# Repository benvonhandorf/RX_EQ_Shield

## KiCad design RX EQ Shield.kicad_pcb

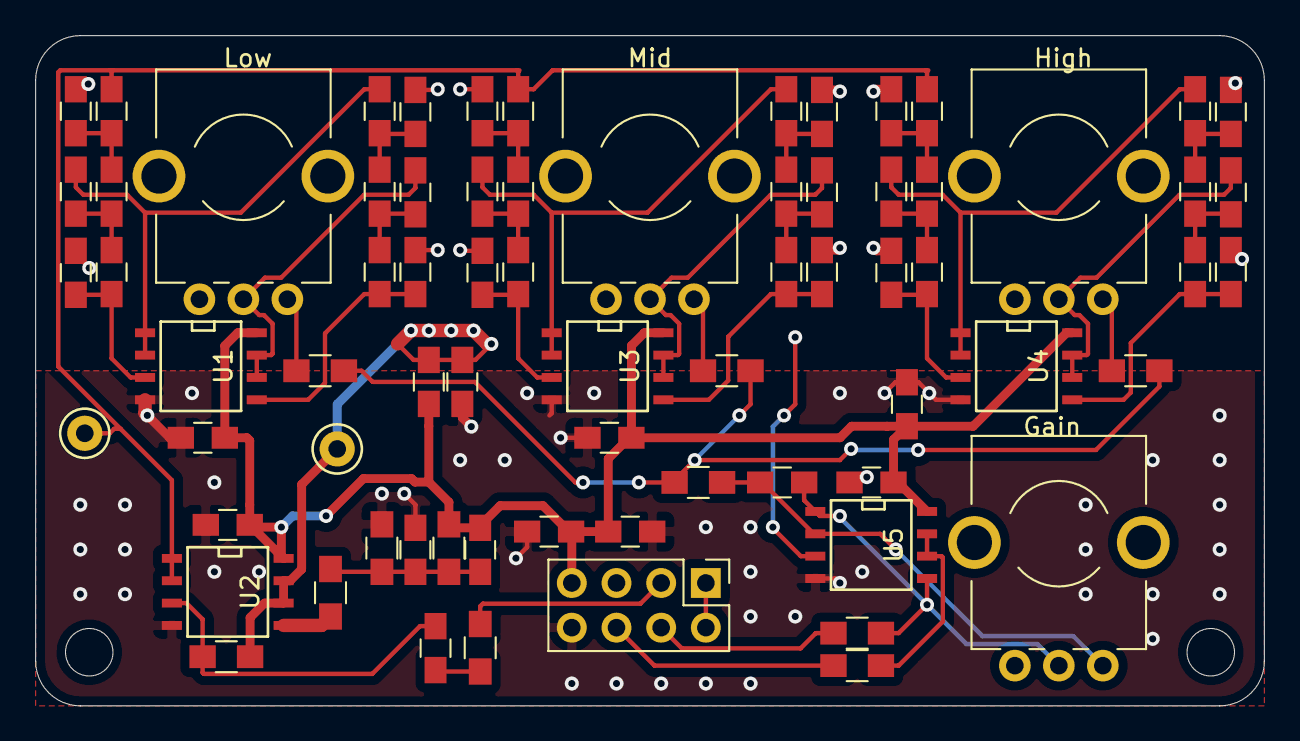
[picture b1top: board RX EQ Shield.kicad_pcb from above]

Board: 2 copper layers, 69.8 x 38.1 mm, 72 parts (0 on the bottom side), 43 nets.

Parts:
A1, A2, A3, A4, A5, A6, A7, A8, A9, A10, A11, A12, A13, A14, A15, A16, A17, A18: C; C_0805_HandSoldering
C1, C6, C8: 10uF; C_0805_HandSoldering
C2, C5, C7: 1uF; C_0805_HandSoldering
C3, C4, C9, C10, C11, C12: 0.1uF; C_0805_HandSoldering
C13: 1nF; C_0805_HandSoldering
FB1, FB2: Ferrite_Bead; L_0805_HandSoldering
J1: Conn_02x04_Odd_Even; Pin_Header_Straight_2x04_Pitch2.54mm
P1, P2, P3, P4, P5, P6, P7, P8, P9, P10, P11, P12, P13, P14, P15, P16, P17, P18: R; C_0805_HandSoldering
R1, R2: 1; R_0805_HandSoldering
R3, R4, R5, R6, R7, R8: 10k; R_0805_HandSoldering
R9: 4.7k; R_0805_HandSoldering
RV1, RV2, RV3, RV4: 10k; Potentiometer_TT_P090S-Top-Adjust
TP4, TP5: TestPoint; Test_Point_Keystone_5000-5004_Miniature
U1, U2, U3, U4, U5: OPA1678; SOIC-8-N

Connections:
+5V: C1.1, C2.1, C3.1, C5.1, C6.1, C9.1, C10.1, C11.1, C12.1, J1.7, R5.1, U1.8, U2.8, U3.8, U4.8, U5.8
/High EQ/AudioFilter/Audio_Out: A16.1, RV3.2, U4.6, U4.7
/High EQ/Audio_In: P1.2, P7.2, P13.2, TP4.1, U2.1, U2.2
/Low EQ/AudioFilter/Audio_Out: A4.1, RV1.2, U1.6, U1.7
/Mid EQ/AudioFilter/Audio_Out: A10.1, RV2.2, U3.6, U3.7
/Mixer/Audio_In: R3.1, R7.1, R8.1, R9.2
/Mixer/Audio_Out_L: C13.1, R1.2, RV4.2, U5.1, U5.5
/Mixer/Audio_Out_R: R2.2, U5.6, U5.7
Audio_In_L: FB1.2, J1.3
Audio_Out_L: J1.4, R1.1
Audio_Out_R: J1.6, R2.1
GND: C1.2, C2.2, C3.2, C7.2, C8.2, C9.2, C10.2, C11.2, C12.2, J1.8, R6.2, U1.4, U2.4, U3.4, U4.4, U5.4
GNDA: A2.2, A3.2, A5.2, A6.2, A8.2, A9.2, A11.2, A12.2, A14.2, A15.2, A17.2, A18.2, C6.2, C8.1, R4.2, TP5.1, U2.6, U2.7, U5.3
Mic_In: J1.1, J1.2
unnamed: A1.1, P4.2, U1.1, U1.2
unnamed: A1.2, P2.1, P3.2
unnamed: A2.1, P1.1, P2.2
unnamed: A3.1, P3.1, U1.3
unnamed: A4.2, P5.1, P6.2
unnamed: A5.1, P4.1, P5.2
unnamed: A6.1, P6.1, U1.5
unnamed: A7.1, P10.2, U3.1, U3.2
unnamed: A7.2, P8.1, P9.2
unnamed: A8.1, P7.1, P8.2
unnamed: A9.1, P9.1, U3.3
unnamed: A10.2, P11.1, P12.2
unnamed: A11.1, P10.1, P11.2
unnamed: A12.1, P12.1, U3.5
unnamed: A13.1, P16.2, U4.1, U4.2
unnamed: A13.2, P14.1, P15.2
unnamed: A14.1, P13.1, P14.2
unnamed: A15.1, P15.1, U4.3
unnamed: A16.2, P17.1, P18.2
unnamed: A17.1, P16.1, P17.2
unnamed: A18.1, P18.1, U4.5
unnamed: C4.1, R4.1, U2.3
unnamed: C4.2, FB1.1
unnamed: C5.2, C7.1, FB2.2, R5.2, R6.1
unnamed: C13.2, R9.1, RV4.3, U5.2
unnamed: FB2.1, U2.5
unnamed: R3.2, RV1.3
unnamed: R7.2, RV2.3
unnamed: R8.2, RV3.3

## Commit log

2020-02-10 WIP - Initial schematics
2020-02-13 Filter calculations, gain stage, oscillation protection
2020-05-17 Ferrite beads and annotations
2020-05-17 Layout, 2020-05 order
2020-06-02 Faceplate WIP
2020-06-02 Faceplate ordered
2022-07-02 Backup
